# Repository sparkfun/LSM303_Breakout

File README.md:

**NOTE:** *This product has been retired from our catalog. If you are looking for more up-to-date info, please check out some of these resources to see how other users are still hacking and improving on this product.*
* *[SparkFun Forum](https://forum.sparkfun.com/)*
* *[IRC Channel](https://www.sparkfun.com/news/263)*

LSM303DLMTR Breakout Board
===========================

[
*LSM303DLMTR Breakout Board (SEN-10888)*](https://www.sparkfun.com/products/10888)

The LSM303DLMTR is a triple axis accelerometer and triple axis magnetic sensor, providing 6D of orientation detection.

There is example code available [here](https://github.com/pololu/lsm303-arduino).

Repository Contents
-------------------
* **/Hardware** - All Eagle design files (.brd, .sch)

License Information
-------------------
The hardware is released under [Creative Commons Share-alike 3.0](http://creativecommons.org/licenses/by-sa/3.0/).

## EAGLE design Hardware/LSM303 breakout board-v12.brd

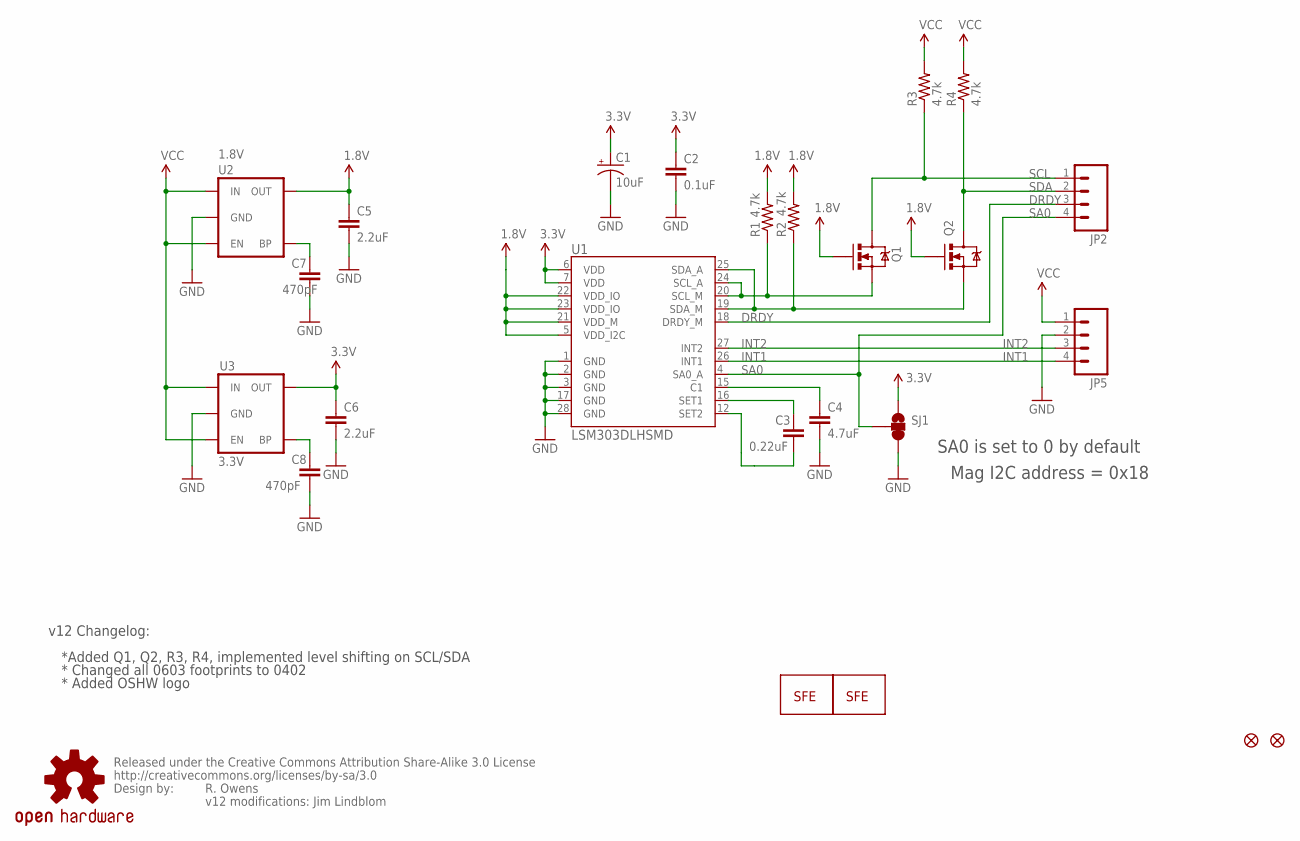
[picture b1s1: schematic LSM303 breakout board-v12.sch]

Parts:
C1: 10uF; EIA3216
C2: 0.1uF; 0402-CAP
C3: 0.22uF; 0402-CAP
C4: 4.7uF; 0402-CAP
C5, C6: 2.2uF; 0402-CAP
C7, C8: 470pF; 0402-CAP
JP1: LOGO-SFENW2; SFE-NEW-WEB
JP2, JP5: M04PTH; 1X04
JP3, JP4: FIDUCIAL1X2; FIDUCIAL-1X2
JP6: LOGO-SFESK; SFE-LOGO-FLAME
Q1, Q2: MOSFET-N-CH; SOT23-3
R1, R2, R3, R4: 4.7k; 0402-RES
SJ1: SOLDERJUMPER_2WAYPASTE2&3; SJ_3_PASTE2&3
U1: LSM303DLHSMD; LGA28-5X5
U2: 1.8V; SC70
U3: 3.3V; SOT23-5
U$5: CREATIVE_COMMONS
U$8: OSHW-LOGOS; OSHW-LOGO-S

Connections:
1.8V: C5.1, Q1.1 (G), Q2.1 (G), R1.2, R2.2, U1.5 (VDD_I2C), U1.21 (VDD_M), U1.22 (VDD_IO), U1.23 (VDD_IO), U2.5 (OUT)
3.3V: C1.A (+), C2.1, C6.1, SJ1.1, U1.6 (VDD), U1.7 (VDD), U3.5 (OUT)
DRDY: JP2.3, U1.18 (DRDY_M)
GND: C1.C (-), C2.2, C4.2, C5.2, C6.2, C7.2, C8.2, JP5.2, SJ1.3, U1.1 (GND), U1.2 (GND), U1.3 (GND), U1.17 (GND), U1.28 (GND), U2.2 (GND), U3.2 (GND)
INT1: JP5.4, U1.26 (INT1)
INT2: JP5.3, U1.27 (INT2)
unnamed: C7.1, U2.4 (BP)
unnamed: C8.1, U3.4 (BP)
unnamed: C3.1, U1.16 (SET1)
unnamed: C3.2, U1.12 (SET2)
unnamed: C4.1, U1.15 (C1)
SA0: JP2.4, SJ1.2, U1.4 (SA0_A)
SCL: JP2.1, Q1.3 (D), R3.1
SCL_M: Q1.2 (S), R1.1, U1.20 (SCL_M), U1.24 (SCL_A)
SDA: JP2.2, Q2.3 (D), R4.1
SDA_M: Q2.2 (S), R2.1, U1.19 (SDA_M), U1.25 (SDA_A)
VCC: JP5.1, R3.2, R4.2, U2.1 (IN), U2.3 (EN), U3.1 (IN), U3.3 (EN)

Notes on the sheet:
R. Owens
v12 modifications: Jim Lindblom
v12 Changelog:
*Added Q1, Q2, R3, R4, implemented level shifting on SCL/SDA
* Changed all 0603 footprints to 0402
SA0 is set to 0 by default
Mag I2C address = 0x18
* Added OSHW logo

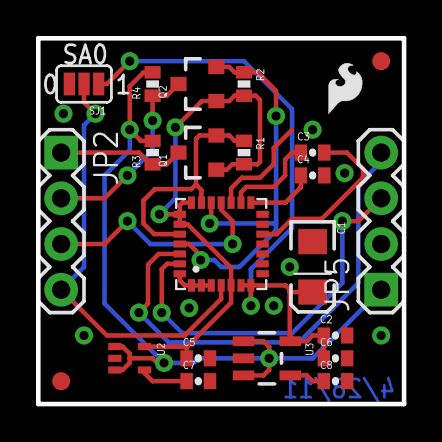
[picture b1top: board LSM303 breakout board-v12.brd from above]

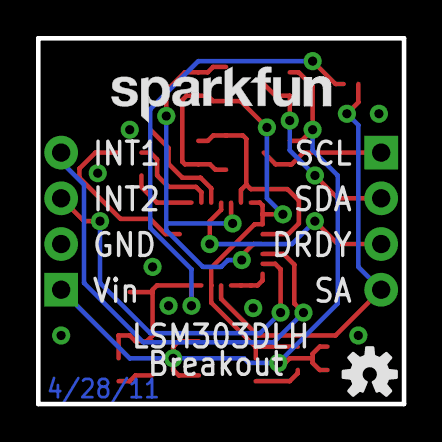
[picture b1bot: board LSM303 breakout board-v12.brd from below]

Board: 2 copper layers, 20.3 x 20.3 mm, 26 parts (2 on the bottom side), 17 nets.

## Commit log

2014-01-10 Adding hardware files and README

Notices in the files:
parts and their libraries:
SparkFun: Released under the Creative Commons Attribution Share-Alike 3.0 License
